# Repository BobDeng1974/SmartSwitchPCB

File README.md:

SmartSwitchPCB
==============

Eagle and Gerber Files for the PCB of the [SmartSwitch](https://github.com/phhe/spark_smartswitch) with the Spark Core.

## Layout 

### Check Layout
1. Open brd-Layout
2. Tools -> DRC
3. Load
4. Choose 'ITEADstudio_DRC.dru' (ftp://imall.iteadstudio.com/PCBs/ITEADstudio_DRC.zip)
5. Check... 

### Generate Gerbers
1. Open brd-Layout
2. File -> CAM Processor
3. File -> Open --> Job ...
4. Choose 'ITeadstudio_CAM6.cam'  (ftp://imall.iteadstudio.com/PCBs/ITEADstudio_CAM%20for%20Eagle6.x.zip)
5. Execute Job...

## Case

The SmartSwitch Case is for the ButtonPad version of the SmartSwitch.
It is based on a Layout from [MakerCase](http://makercase.com) and the  [Arduinome eXperimenter’s Case](http://interactives.artsrn.ualberta.ca/?page_id=133).

The *.eps file can be ordered at [ponoko.com](http://ponoko.com) or [formulor.de](http://formulor.de)

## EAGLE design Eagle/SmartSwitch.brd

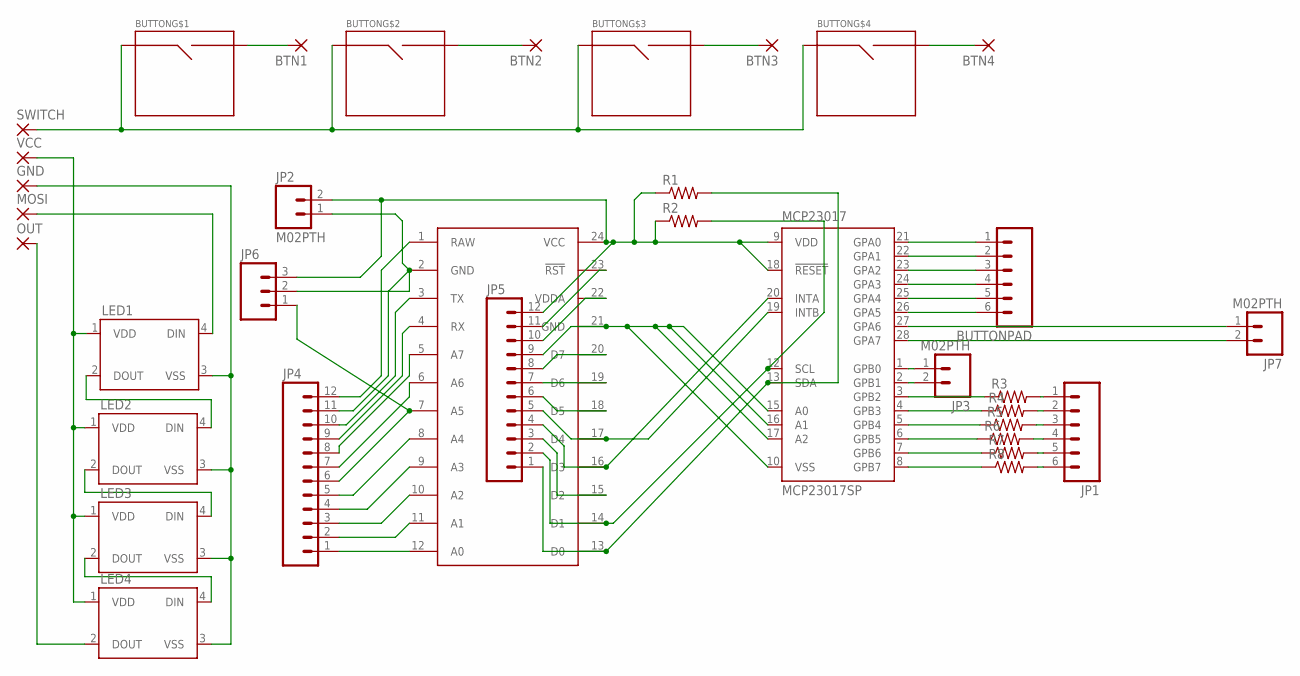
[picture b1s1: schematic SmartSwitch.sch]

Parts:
BTN1, BTN2, BTN3, BTN4: 2,15/1,0
BUTTON: BUTTON
BUTTONPAD: M06SILK_FEMALE_PTH; 1X06
GND: 2,15/1,0
JP1: M06SILK_FEMALE_PTH; 1X06
JP2, JP3, JP7: M02PTH; 1X02
JP4, JP5: M12PTH; 1X12-SMALL-PADS
JP6: M03PTH; 1X03
LED1, LED2, LED3, LED4: WS2812B
MCP23017: MCP23017SP; DIL28-3
MOSI: 2,15/1,0
OUT: 2,15/1,0
R1, R2, R3, R4, R5, R6, R7, R8: RESISTORPTH-1/4W; AXIAL-0.4
SPARK: SPARK_CORECORE; SPARK_CORE
SWITCH: 2,15/1,0
VCC: 2,15/1,0

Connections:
GROUND: GND.1, LED1.3 (VSS), LED2.3 (VSS), LED3.3 (VSS), LED4.3 (VSS)
MOSI: LED1.4 (DIN), MOSI.1
unnamed: BTN1.1, BUTTON.SIG2
unnamed: BTN2.1, BUTTON.SIG4 (SIG2)
unnamed: BTN3.1, BUTTON.SIG6 (SIG2)
unnamed: BTN4.1, BUTTON.SIG8 (SIG2)
unnamed: BUTTONPAD.1, MCP23017.21 (GPA0)
unnamed: BUTTONPAD.2, MCP23017.22 (GPA1)
unnamed: BUTTONPAD.3, MCP23017.23 (GPA2)
unnamed: BUTTONPAD.4, MCP23017.24 (GPA3)
unnamed: LED4.2 (DOUT), OUT.1
unnamed: LED1.1 (VDD), LED2.1 (VDD), LED3.1 (VDD), LED4.1 (VDD), VCC.1
unnamed: LED1.2 (DOUT), LED2.4 (DIN)
unnamed: LED2.2 (DOUT), LED3.4 (DIN)
unnamed: LED3.2 (DOUT), LED4.4 (DIN)
unnamed: BUTTONPAD.5, MCP23017.25 (GPA4)
unnamed: BUTTONPAD.6, MCP23017.26 (GPA5)
unnamed: JP7.1, MCP23017.27 (GPA6)
unnamed: JP7.2, MCP23017.28 (GPA7)
unnamed: JP3.1, MCP23017.1 (GPB0)
unnamed: JP3.2, MCP23017.2 (GPB1)
unnamed: MCP23017.3 (GPB2), R3.P$1 (1)
unnamed: JP1.1, R3.P$2 (2)
unnamed: JP1.2, R4.P$2 (2)
unnamed: JP1.3, R5.P$2 (2)
unnamed: JP1.4, R6.P$2 (2)
unnamed: JP1.5, R7.P$2 (2)
unnamed: JP5.3, SPARK.15 (D2)
unnamed: JP5.5, MCP23017.19 (INTB), SPARK.17 (D4)
unnamed: JP2.2, JP5.12, JP6.3, MCP23017.9 (VDD), MCP23017.18 (!RESET), R1.P$1 (1), R2.P$1 (1), SPARK.24 (VCC)
unnamed: JP4.6, JP6.1, SPARK.7 (A5)
unnamed: JP2.1, JP4.11, JP6.2, SPARK.2 (GND)
unnamed: JP4.1, SPARK.12 (A0)
unnamed: JP5.9, MCP23017.10 (VSS), MCP23017.15 (A0), MCP23017.16 (A1), MCP23017.17 (A2), SPARK.21 (GND)
unnamed: JP5.2, MCP23017.12 (SCL), R2.P$2 (2), SPARK.14 (D1)
unnamed: JP5.1, MCP23017.13 (SDA), R1.P$2 (2), SPARK.13 (D0)
unnamed: JP4.2, SPARK.11 (A1)
unnamed: JP4.3, SPARK.10 (A2)
unnamed: JP4.4, SPARK.9 (A3)
unnamed: JP4.5, SPARK.8 (A4)
unnamed: JP4.7, SPARK.6 (A6)
unnamed: JP4.8, SPARK.5 (A7)
unnamed: JP4.9, SPARK.4 (RX)
unnamed: JP4.10, SPARK.3 (TX)
unnamed: JP5.6, SPARK.18 (D5)
unnamed: JP4.12, SPARK.1 (RAW)
unnamed: JP1.6, R8.P$2 (2)
unnamed: JP5.8, SPARK.20 (D7)
unnamed: JP5.7, SPARK.19 (D6)
unnamed: JP5.10, SPARK.22 (VDDA)
unnamed: JP5.11, SPARK.23 (!RST)
unnamed: BUTTON.SIG1, BUTTON.SIG3 (SIG1), BUTTON.SIG5 (SIG1), BUTTON.SIG7 (SIG1), SWITCH.1
unnamed: JP5.4, MCP23017.20 (INTA), SPARK.16 (D3)
unnamed: MCP23017.8 (GPB7), R8.P$1 (1)
unnamed: MCP23017.7 (GPB6), R7.P$1 (1)
unnamed: MCP23017.6 (GPB5), R6.P$1 (1)
unnamed: MCP23017.5 (GPB4), R5.P$1 (1)
unnamed: MCP23017.4 (GPB3), R4.P$1 (1)

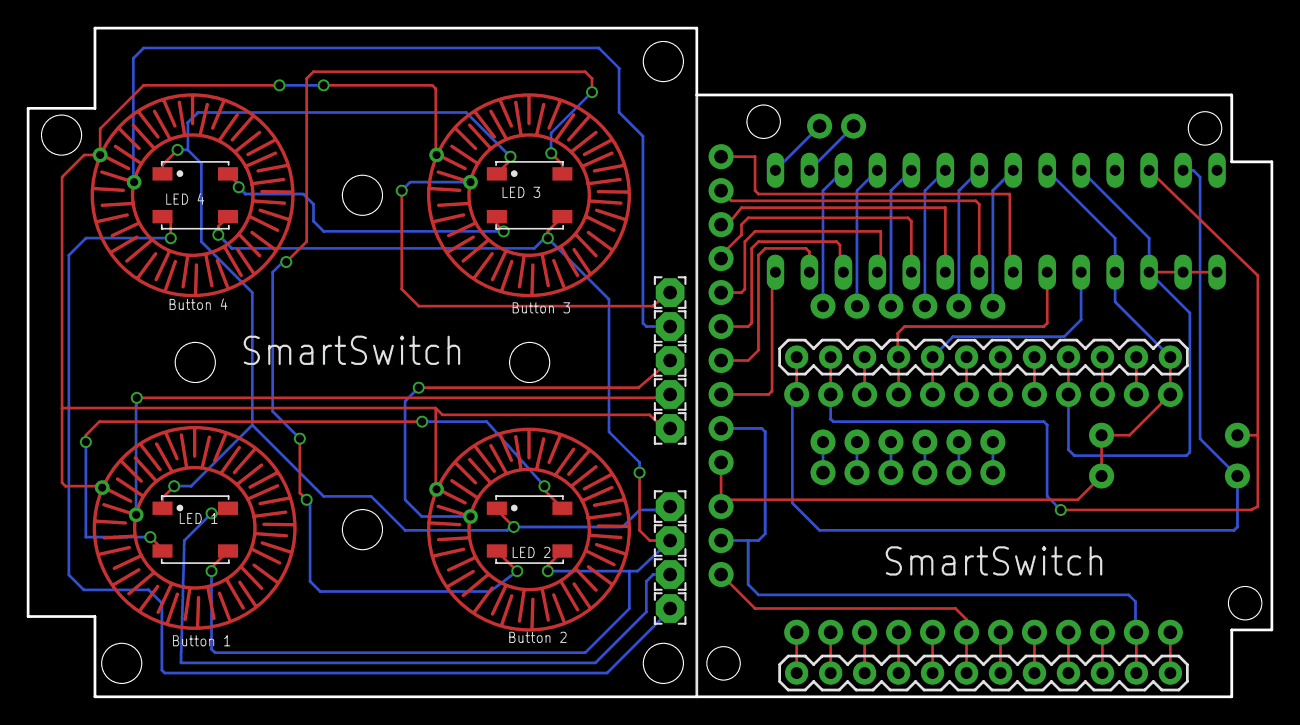
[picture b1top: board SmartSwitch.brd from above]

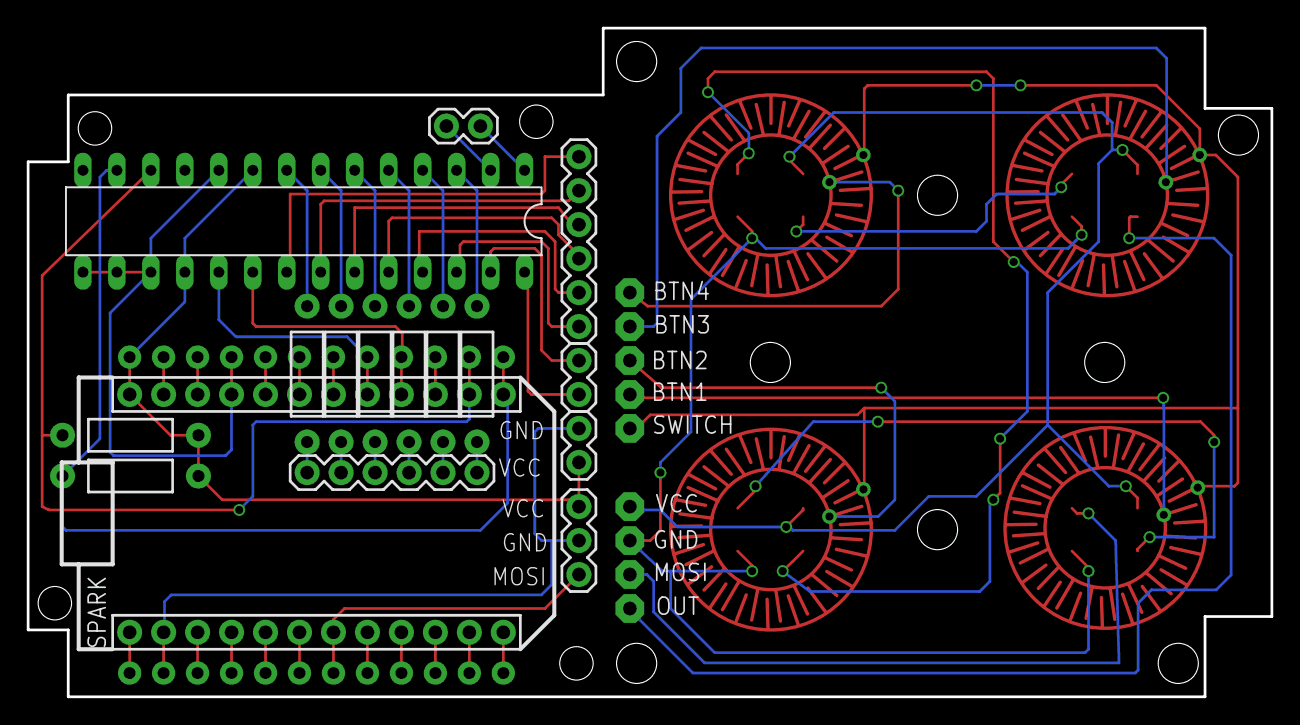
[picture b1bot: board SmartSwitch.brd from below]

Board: 2 copper layers, 93.0 x 50.0 mm, 32 parts (16 on the bottom side), 58 nets.

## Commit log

2014-12-11 Initial Commit
    Bugfix short-circuit
2014-12-11 Update WS2812B Positions
2014-12-11 Image Export
2014-12-12 Change GND/VCC on Buttonpad connection
2014-12-12 Move resistors
2014-12-15 series resistor, edges
2014-12-15 Change Jumper
2014-12-15 Resistors
2015-01-21 Added Case Modell

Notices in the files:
parts and their libraries:
SparkFun-LED: Licensing: Creative Commons ShareAlike 4.0 International - https://creativecommons.org/licenses/by-sa/4.0
